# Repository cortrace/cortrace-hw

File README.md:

# cortrace-hw
Cortrace Hardware Design KiCad Project

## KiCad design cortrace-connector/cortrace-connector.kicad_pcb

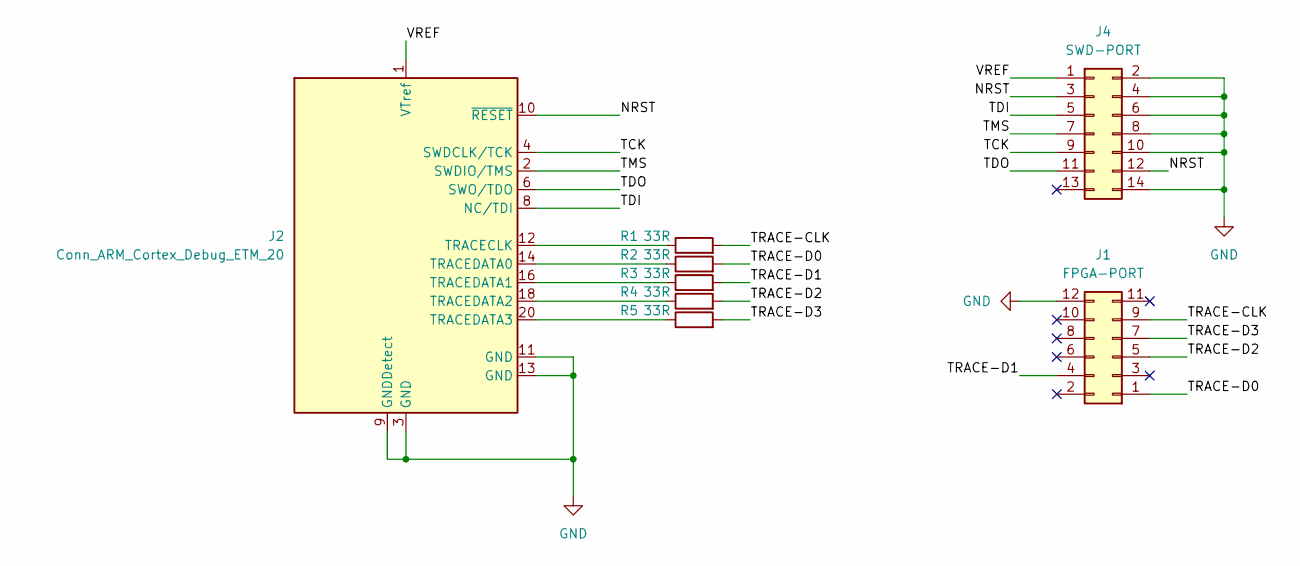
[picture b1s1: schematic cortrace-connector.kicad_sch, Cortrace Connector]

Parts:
J1: FPGA-PORT; PinHeader_2x06_P2.54mm_Vertical
J2: Conn_ARM_Cortex_Debug_ETM_20; PinSocket_2x10_P1.27mm_Vertical_SMD
J4: SWD-PORT; PinHeader_2x07_P2.54mm_Vertical
R1, R2, R3, R4, R5: 33R; C_0402_1005Metric

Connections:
/NRST: J2.10 (~RESET), J4.3, J4.12
/TCK: J2.4 (SWDCLK/TCK), J4.9
/TDI: J2.8 (NC/TDI), J4.5
/TDO: J2.6 (SWO/TDO), J4.11
/TMS: J2.2 (SWDIO/TMS), J4.7
/TRACE-CLK: J1.9, R1.2
/TRACE-D0: J1.1, R2.2
/TRACE-D1: J1.4, R3.2
/TRACE-D2: J1.5, R4.2
/TRACE-D3: J1.7, R5.2
/VREF: J2.1 (VTref), J4.1
GND: J1.12, J2.3 (GND), J2.5 (GND), J2.9 (GNDDetect), J2.11 (GND), J2.13 (GND), J2.15 (GND), J2.17 (GND), J2.19 (GND), J4.2, J4.4, J4.6, J4.8, J4.10, J4.14
unnamed: J2.12 (TRACECLK), R1.1
unnamed: J2.14 (TRACEDATA0), R2.1
unnamed: J2.16 (TRACEDATA1), R3.1
unnamed: J2.18 (TRACEDATA2), R4.1
unnamed: J2.20 (TRACEDATA3), R5.1

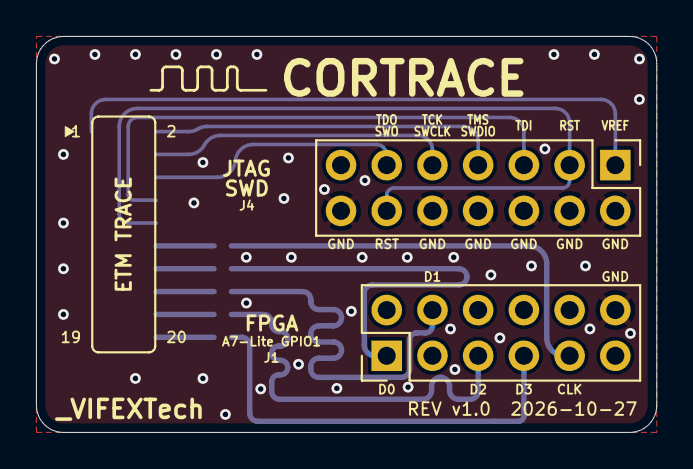
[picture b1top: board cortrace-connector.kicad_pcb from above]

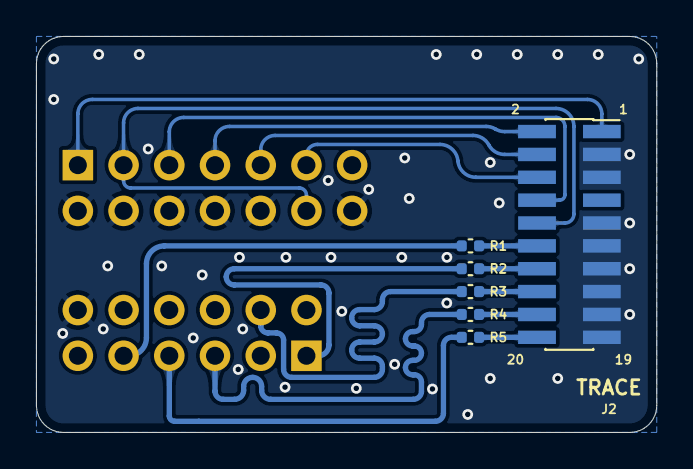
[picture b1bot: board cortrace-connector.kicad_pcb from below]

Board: 2 copper layers, 34.5 x 22.0 mm, 8 parts (6 on the bottom side), 17 nets.
